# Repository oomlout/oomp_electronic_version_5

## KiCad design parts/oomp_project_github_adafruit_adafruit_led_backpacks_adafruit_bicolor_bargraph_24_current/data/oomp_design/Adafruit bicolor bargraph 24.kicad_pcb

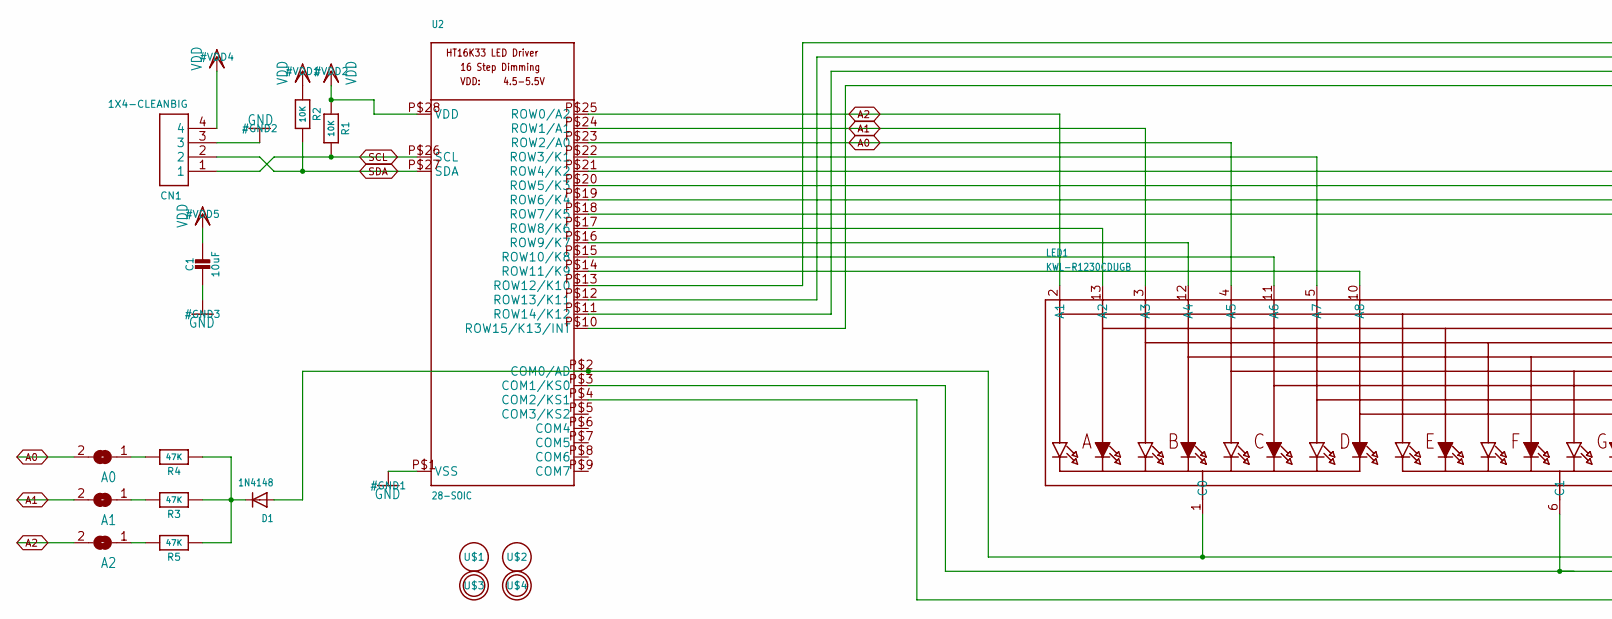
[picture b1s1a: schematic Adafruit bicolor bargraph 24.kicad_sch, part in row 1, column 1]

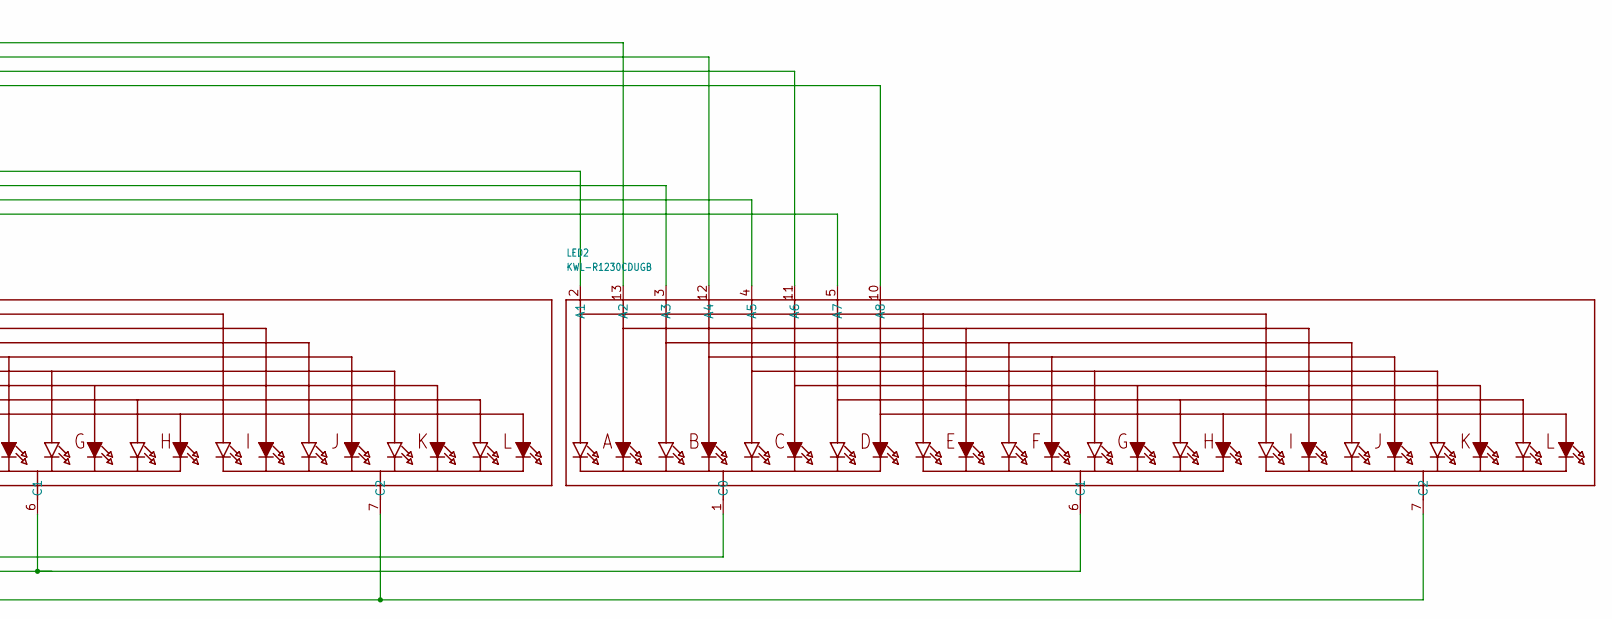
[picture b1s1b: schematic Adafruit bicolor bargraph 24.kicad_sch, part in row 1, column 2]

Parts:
A0, A1, A2: SOLDERJUMPERREFLOW_NOPASTE; SOLDERJUMPER_REFLOW_NOPASTE
C1: 10uF; 0805-NO
CN1: 1X4-CLEANBIG; 1X04-CLEANBIG
D1: 1N4148; SOD-323F
LED1, LED2: KWL-R1230CDUGB; SEGMENT_BICOL_BL-AR12Z3010
R1, R2: 10K; 0805-NO
R3, R4, R5: 47K; 0805-NO
U2: 28-SOIC; SOP28_300MIL
U$1, U$2: FIDUCIAL; FIDUCIAL_1MM
U$3, U$4: MOUNTINGHOLE2.5; MOUNTINGHOLE_2.5_PLATED

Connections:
A0: A0.2, LED1.4 (A5), U2.P$23 (ROW2/A0)
A1: A1.2, LED1.3 (A3), U2.P$24 (ROW1/A1)
A2: A2.2, LED1.2 (A1), U2.P$25 (ROW0/A2)
C0: D1.A, LED1.1 (C0), LED2.1 (C0), U2.P$2 (COM0/AD)
C1: LED1.6 (C1), LED2.6 (C1), U2.P$3 (COM1/KS0)
C2: LED1.7 (C2), LED2.7 (C2), U2.P$4 (COM2/KS1)
GND: C1.2, CN1.3, U2.P$1 (VSS)
unnamed: LED2.5 (A7), U2.P$18 (ROW7/K5)
unnamed: LED1.13 (A2), U2.P$17 (ROW8/K6)
unnamed: LED2.4 (A5), U2.P$19 (ROW6/K4)
unnamed: A2.1, R5.2
unnamed: D1.C, R3.1, R4.1, R5.1
unnamed: A1.1, R3.2
unnamed: A0.1, R4.2
unnamed: LED2.2 (A1), U2.P$21 (ROW4/K2)
unnamed: LED1.5 (A7), U2.P$22 (ROW3/K1)
unnamed: LED2.3 (A3), U2.P$20 (ROW5/K3)
unnamed: LED1.12 (A4), U2.P$16 (ROW9/K7)
R10: LED1.11 (A6), U2.P$15 (ROW10/K8)
R11: LED1.10 (A8), U2.P$14 (ROW11/K9)
R12: LED2.13 (A2), U2.P$13 (ROW12/K10)
R13: LED2.12 (A4), U2.P$12 (ROW13/K11)
R14: LED2.11 (A6), U2.P$11 (ROW14/K12)
R15: LED2.10 (A8), U2.P$10 (ROW15/K13/INT)
SCL: CN1.1, R1.2, U2.P$26 (SCL)
SDA: CN1.2, R2.2, U2.P$27 (SDA)
VDD: C1.1, CN1.4, R1.1, R2.1, U2.P$28 (VDD)

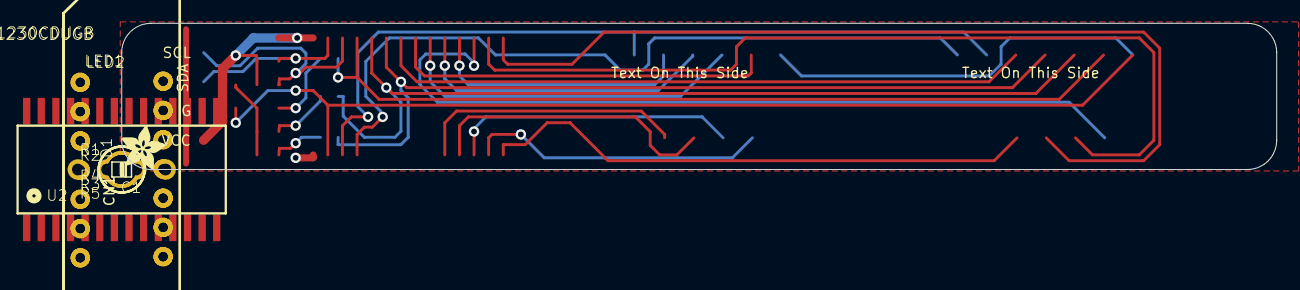
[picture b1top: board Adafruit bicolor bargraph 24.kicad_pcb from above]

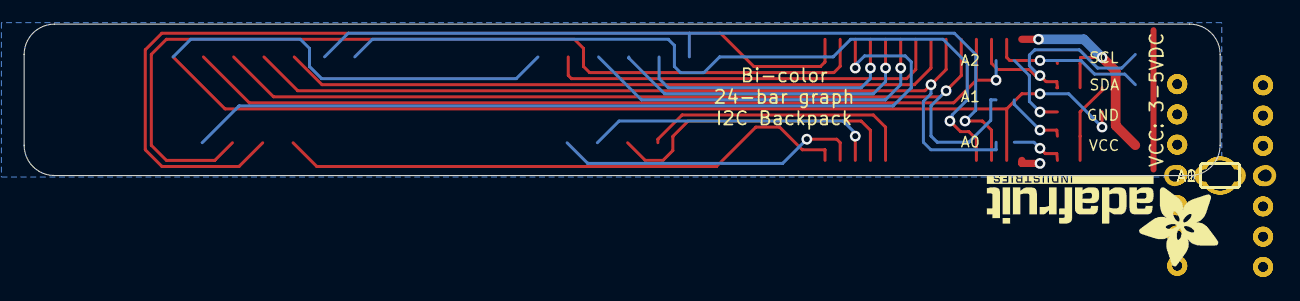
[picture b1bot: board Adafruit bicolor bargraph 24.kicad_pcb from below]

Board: 2 copper layers, 100.3 x 12.7 mm, 20 parts (4 on the bottom side), 27 nets.

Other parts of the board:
U$5: ADAFRUIT_TEXT_20MM
U$6: ADAFRUIT_3.5MM

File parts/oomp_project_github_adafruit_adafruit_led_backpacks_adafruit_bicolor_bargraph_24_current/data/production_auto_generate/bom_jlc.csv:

Comment,Designator,Footprint,LCSC Part #
,U$6,Adafruit bicolor bargraph 24-import-fps:ADAFRUIT_3.5MM,
,U$5,Adafruit bicolor bargraph 24-import-fps:ADAFRUIT_TEXT_20MM,
,"A0,A1,A2",Adafruit bicolor bargraph 24-import-fps:SOLDERJUMPER_REFLOW_NOPASTE,
10K,"R1,R2",Adafruit bicolor bargraph 24-import-fps:0805-NO,C17414
10uF,C1,Adafruit bicolor bargraph 24-import-fps:0805-NO,
1N4148,D1,Adafruit bicolor bargraph 24-import-fps:SOD-323F,
1X4-CLEANBIG,CN1,Adafruit bicolor bargraph 24-import-fps:1X04-CLEANBIG,
28-SOIC,U2,Adafruit bicolor bargraph 24-import-fps:SOP28_300MIL,
47K,"R3,R4,R5",Adafruit bicolor bargraph 24-import-fps:0805-NO,C17713
FIDUCIAL,"U$1,U$2",Adafruit bicolor bargraph 24-import-fps:FIDUCIAL_1MM,
KWL-R1230CDUGB,"LED1,LED2",Adafruit bicolor bargraph 24-import-fps:SEGMENT_BICOL_BL-AR12Z3010,

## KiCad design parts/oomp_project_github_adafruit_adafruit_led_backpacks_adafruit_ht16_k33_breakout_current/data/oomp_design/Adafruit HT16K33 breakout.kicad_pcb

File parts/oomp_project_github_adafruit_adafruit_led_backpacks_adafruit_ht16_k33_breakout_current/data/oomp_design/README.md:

# OOMP KiCad design copy

Open `Adafruit HT16K33 breakout.kicad_pro` (or the `.kicad_pcb` / `.kicad_sch`) in KiCad. Local OOMP libraries are under `libraries/`. Original inputs are preserved in [../original/](../original/).

Only verified unchanged installed KiCad defaults were renamed. Modified, custom, unmatched and unavailable items remain unchanged. Soldering variants are never swapped during conversion. Existing pad coordinates, nets and UUIDs are preserved.

See [conversion_report.yaml](conversion_report.yaml) for every conversion and skip. Copy this directory before editing; regeneration refuses to overwrite edited design files.

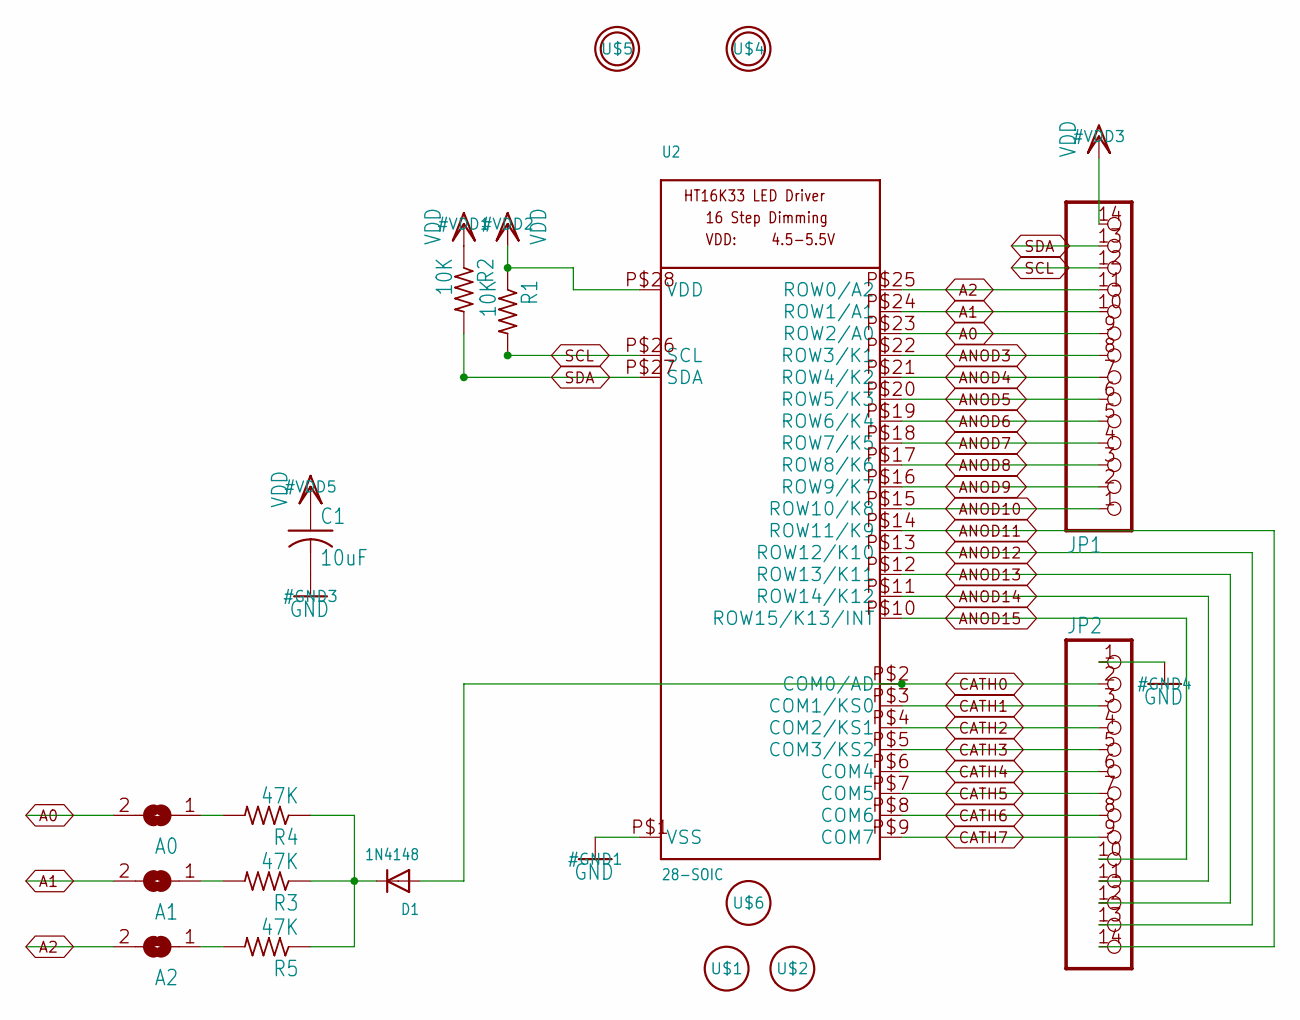
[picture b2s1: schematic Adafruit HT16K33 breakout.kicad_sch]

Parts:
A0, A1, A2: SOLDERJUMPERREFLOW_NOPASTE; SOLDERJUMPER_REFLOW_NOPASTE
C1: 10uF; C0805
D1: 1N4148; SOD-323F
JP1, JP2: PINHD-1X14-CB; 1X14-CB
R1, R2: 10K; R0805
R3, R4, R5: 47K; R0805
U2: 28-SOIC; SOP28_300MIL
U$1, U$2, U$6: FIDUCIAL; FIDUCIAL_1MM
U$4, U$5: MOUNTINGHOLE2.5; MOUNTINGHOLE_2.5_PLATED

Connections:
A0: A0.2, JP1.9, U2.P$23 (ROW2/A0)
A1: A1.2, JP1.10, U2.P$24 (ROW1/A1)
A2: A2.2, JP1.11, U2.P$25 (ROW0/A2)
ANOD3: JP1.8, U2.P$22 (ROW3/K1)
ANOD4: JP1.7, U2.P$21 (ROW4/K2)
ANOD5: JP1.6, U2.P$20 (ROW5/K3)
ANOD6: JP1.5, U2.P$19 (ROW6/K4)
ANOD7: JP1.4, U2.P$18 (ROW7/K5)
ANOD8: JP1.3, U2.P$17 (ROW8/K6)
ANOD9: JP1.2, U2.P$16 (ROW9/K7)
ANOD10: JP1.1, U2.P$15 (ROW10/K8)
ANOD11: JP2.14, U2.P$14 (ROW11/K9)
ANOD12: JP2.13, U2.P$13 (ROW12/K10)
ANOD13: JP2.12, U2.P$12 (ROW13/K11)
ANOD14: JP2.11, U2.P$11 (ROW14/K12)
ANOD15: JP2.10, U2.P$10 (ROW15/K13/INT)
CATH0: D1.A, JP2.2, U2.P$2 (COM0/AD)
CATH1: JP2.3, U2.P$3 (COM1/KS0)
CATH2: JP2.4, U2.P$4 (COM2/KS1)
CATH3: JP2.5, U2.P$5 (COM3/KS2)
CATH4: JP2.6, U2.P$6 (COM4)
CATH5: JP2.7, U2.P$7 (COM5)
CATH6: JP2.8, U2.P$8 (COM6)
CATH7: JP2.9, U2.P$9 (COM7)
GND: C1.2, JP2.1, U2.P$1 (VSS)
unnamed: A2.1, R5.2
unnamed: D1.C, R3.1, R4.1, R5.1
unnamed: A1.1, R3.2
unnamed: A0.1, R4.2
SCL: JP1.12, R1.2, U2.P$26 (SCL)
SDA: JP1.13, R2.2, U2.P$27 (SDA)
VDD: C1.1, JP1.14, R1.1, R2.1, U2.P$28 (VDD)

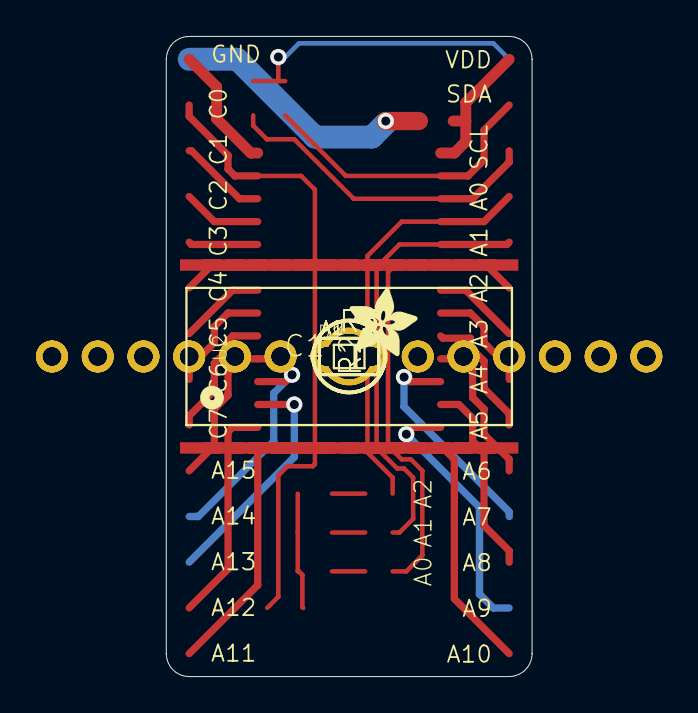
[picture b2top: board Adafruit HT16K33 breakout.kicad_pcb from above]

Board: 16 copper layers, 20.3 x 35.6 mm, 20 parts (1 on the bottom side), 32 nets.

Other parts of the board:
U$3: ADAFRUIT_3.5MM
U$7: ADAFRUIT_5MM

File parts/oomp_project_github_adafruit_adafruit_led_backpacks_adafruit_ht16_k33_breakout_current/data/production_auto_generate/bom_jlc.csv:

Comment,Designator,Footprint,LCSC Part #
,"JP1,JP2",Adafruit HT16K33 breakout-import-fps:1X14-CB,C2905490
,U$3,Adafruit HT16K33 breakout-import-fps:ADAFRUIT_3.5MM,
,U$7,Adafruit HT16K33 breakout-import-fps:ADAFRUIT_5MM,
,"A0,A1,A2",Adafruit HT16K33 breakout-import-fps:SOLDERJUMPER_REFLOW_NOPASTE,
10K,"R1,R2",Adafruit HT16K33 breakout-import-fps:R0805,C17414
10uF,C1,Adafruit HT16K33 breakout-import-fps:C0805,
1N4148,D1,Adafruit HT16K33 breakout-import-fps:SOD-323F,
28-SOIC,U2,Adafruit HT16K33 breakout-import-fps:SOP28_300MIL,
47K,"R3,R4,R5",Adafruit HT16K33 breakout-import-fps:R0805,C17713
FIDUCIAL,"U$1,U$2,U$6",Adafruit HT16K33 breakout-import-fps:FIDUCIAL_1MM,

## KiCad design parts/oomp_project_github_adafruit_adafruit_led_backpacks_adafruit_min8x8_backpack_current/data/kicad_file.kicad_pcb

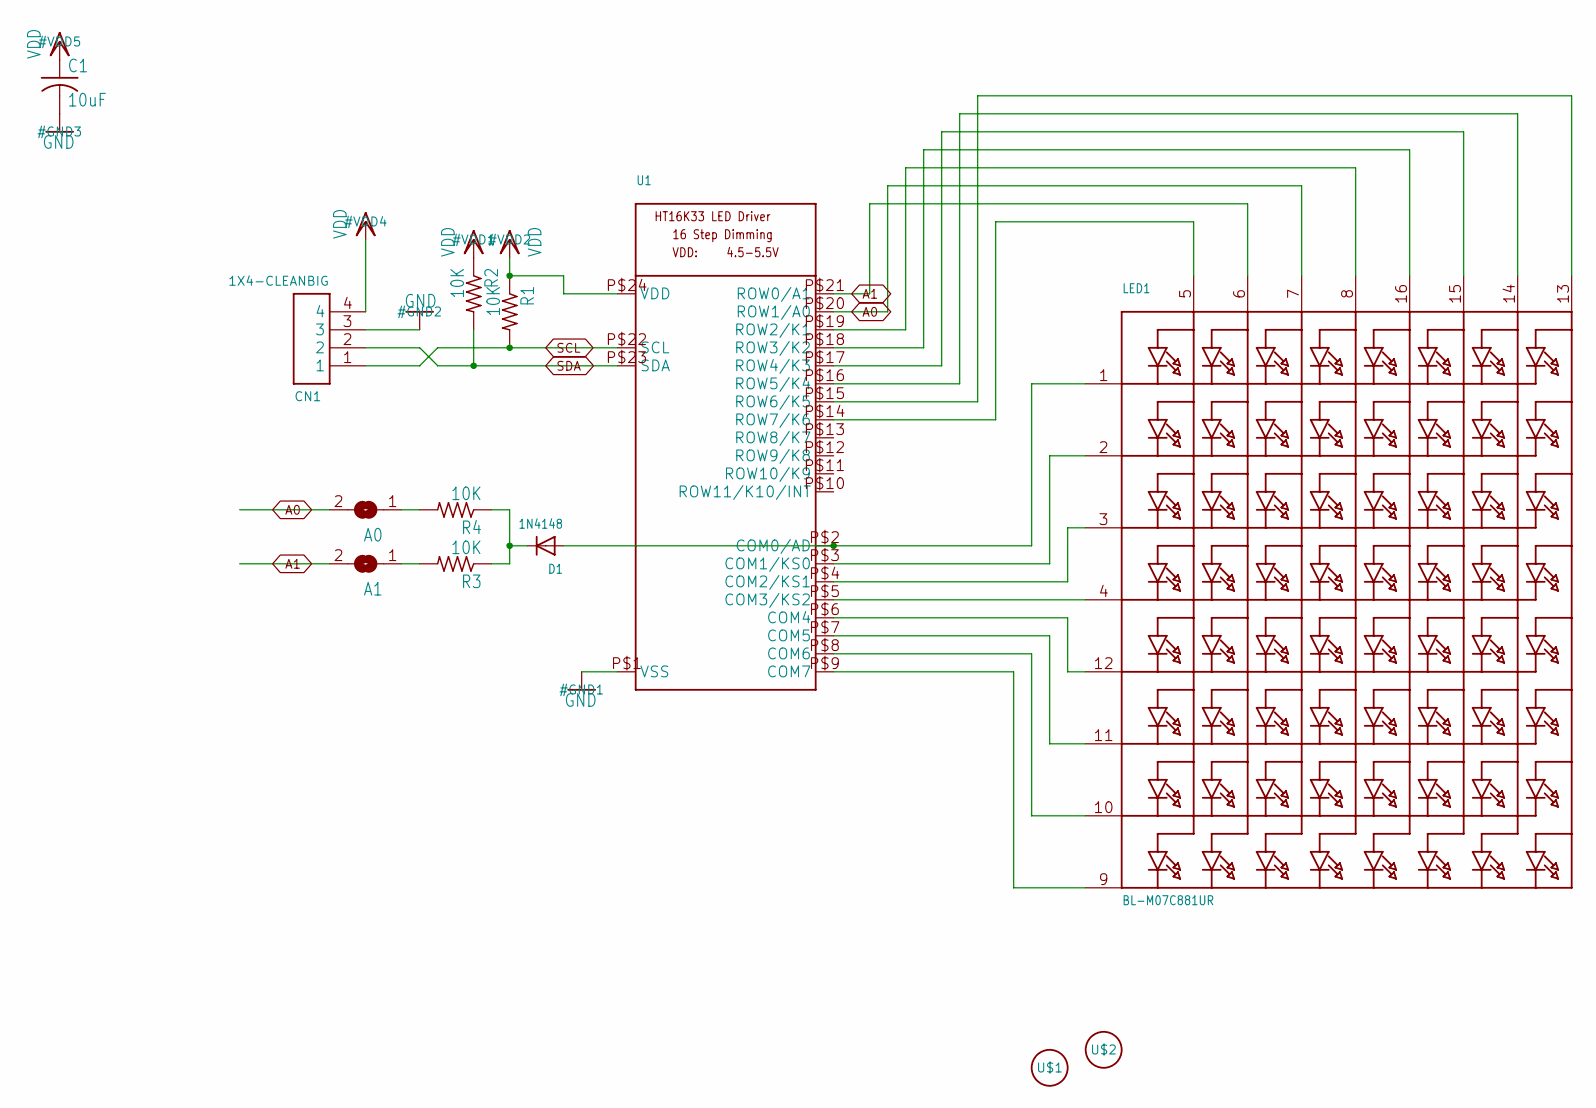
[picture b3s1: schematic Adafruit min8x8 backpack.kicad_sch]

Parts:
A0, A1: SOLDERJUMPERREFLOW_NOPASTE; SOLDERJUMPER_REFLOW_NOPASTE
C1: 10uF; C0805
CN1: 1X4-CLEANBIG; 1X04-CLEANBIG
D1: 1N4148; SOD-323F
LED1: BL-M07C881UR; SEGMENT_BL-M07C881UR
R1, R2, R3, R4: 10K; R0805
U1: HT16K33_SOP24; SOP24_300MIL
U$1, U$2: FIDUCIAL; FIDUCIAL_1MM

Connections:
A0: A0.2, LED1.7 (A3), U1.P$20 (ROW1/A0)
A1: A1.2, LED1.6 (A2), U1.P$21 (ROW0/A1)
GND: C1.2, CN1.3, U1.P$1 (VSS)
unnamed: LED1.9 (K8), U1.P$9 (COM7)
unnamed: LED1.10 (K7), U1.P$8 (COM6)
unnamed: LED1.11 (K6), U1.P$7 (COM5)
unnamed: LED1.12 (K5), U1.P$6 (COM4)
unnamed: LED1.4 (K4), U1.P$5 (COM3/KS2)
unnamed: LED1.3 (K3), U1.P$4 (COM2/KS1)
unnamed: LED1.2 (K2), U1.P$3 (COM1/KS0)
unnamed: D1.A, LED1.1 (K1), U1.P$2 (COM0/AD)
unnamed: LED1.8 (A4), U1.P$19 (ROW2/K1)
unnamed: LED1.16 (A5), U1.P$18 (ROW3/K2)
unnamed: LED1.15 (A6), U1.P$17 (ROW4/K3)
unnamed: D1.C, R3.1, R4.1
unnamed: LED1.5 (A1), U1.P$14 (ROW7/K6)
unnamed: A1.1, R3.2
unnamed: A0.1, R4.2
SCL: CN1.1, R1.2, U1.P$22 (SCL)
SDA: CN1.2, R2.2, U1.P$23 (SDA)
SEG_F: LED1.14 (A7), U1.P$16 (ROW5/K4)
SEG_G: LED1.13 (A8), U1.P$15 (ROW6/K5)
VDD: C1.1, CN1.4, R1.1, R2.1, U1.P$24 (VDD)

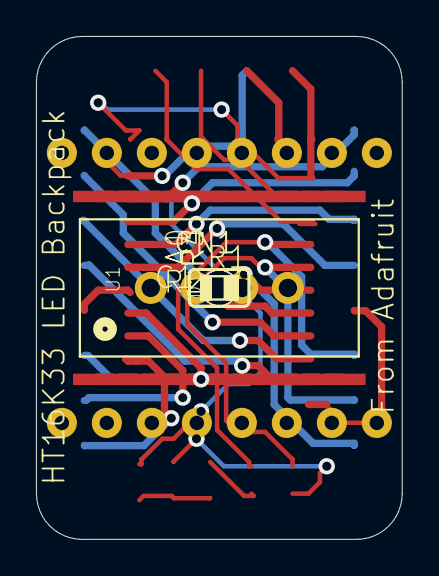
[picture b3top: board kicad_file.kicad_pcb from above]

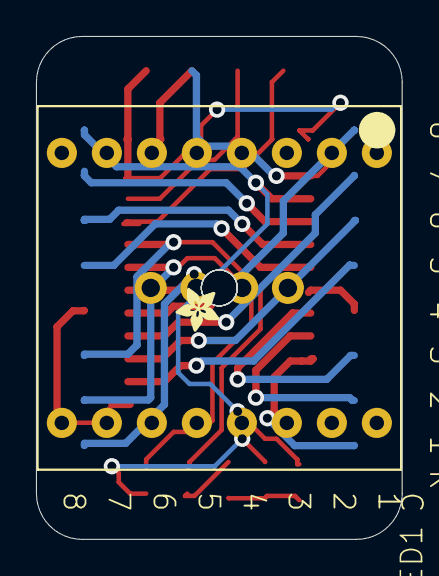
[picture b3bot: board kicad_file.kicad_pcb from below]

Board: 16 copper layers, 20.3 x 27.9 mm, 18 parts (2 on the bottom side), 23 nets.

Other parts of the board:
U$4: ADAFRUIT_2.5MM
UNK_HOLE_0: dummyfp0
UNK_HOLE_1: dummyfp1
UNK_HOLE_2: dummyfp2
UNK_HOLE_3: dummyfp3

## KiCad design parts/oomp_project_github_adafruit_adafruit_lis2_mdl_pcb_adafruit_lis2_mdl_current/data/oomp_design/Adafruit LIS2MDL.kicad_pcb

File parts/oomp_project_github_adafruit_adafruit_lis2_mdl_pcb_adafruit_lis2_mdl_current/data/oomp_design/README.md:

# OOMP KiCad design copy

Open `Adafruit LIS2MDL.kicad_pro` (or the `.kicad_pcb` / `.kicad_sch`) in KiCad. Local OOMP libraries are under `libraries/`. Original inputs are preserved in [../original/](../original/).

Only verified unchanged installed KiCad defaults were renamed. Modified, custom, unmatched and unavailable items remain unchanged. Soldering variants are never swapped during conversion. Existing pad coordinates, nets and UUIDs are preserved.

See [conversion_report.yaml](conversion_report.yaml) for every conversion and skip. Copy this directory before editing; regeneration refuses to overwrite edited design files.

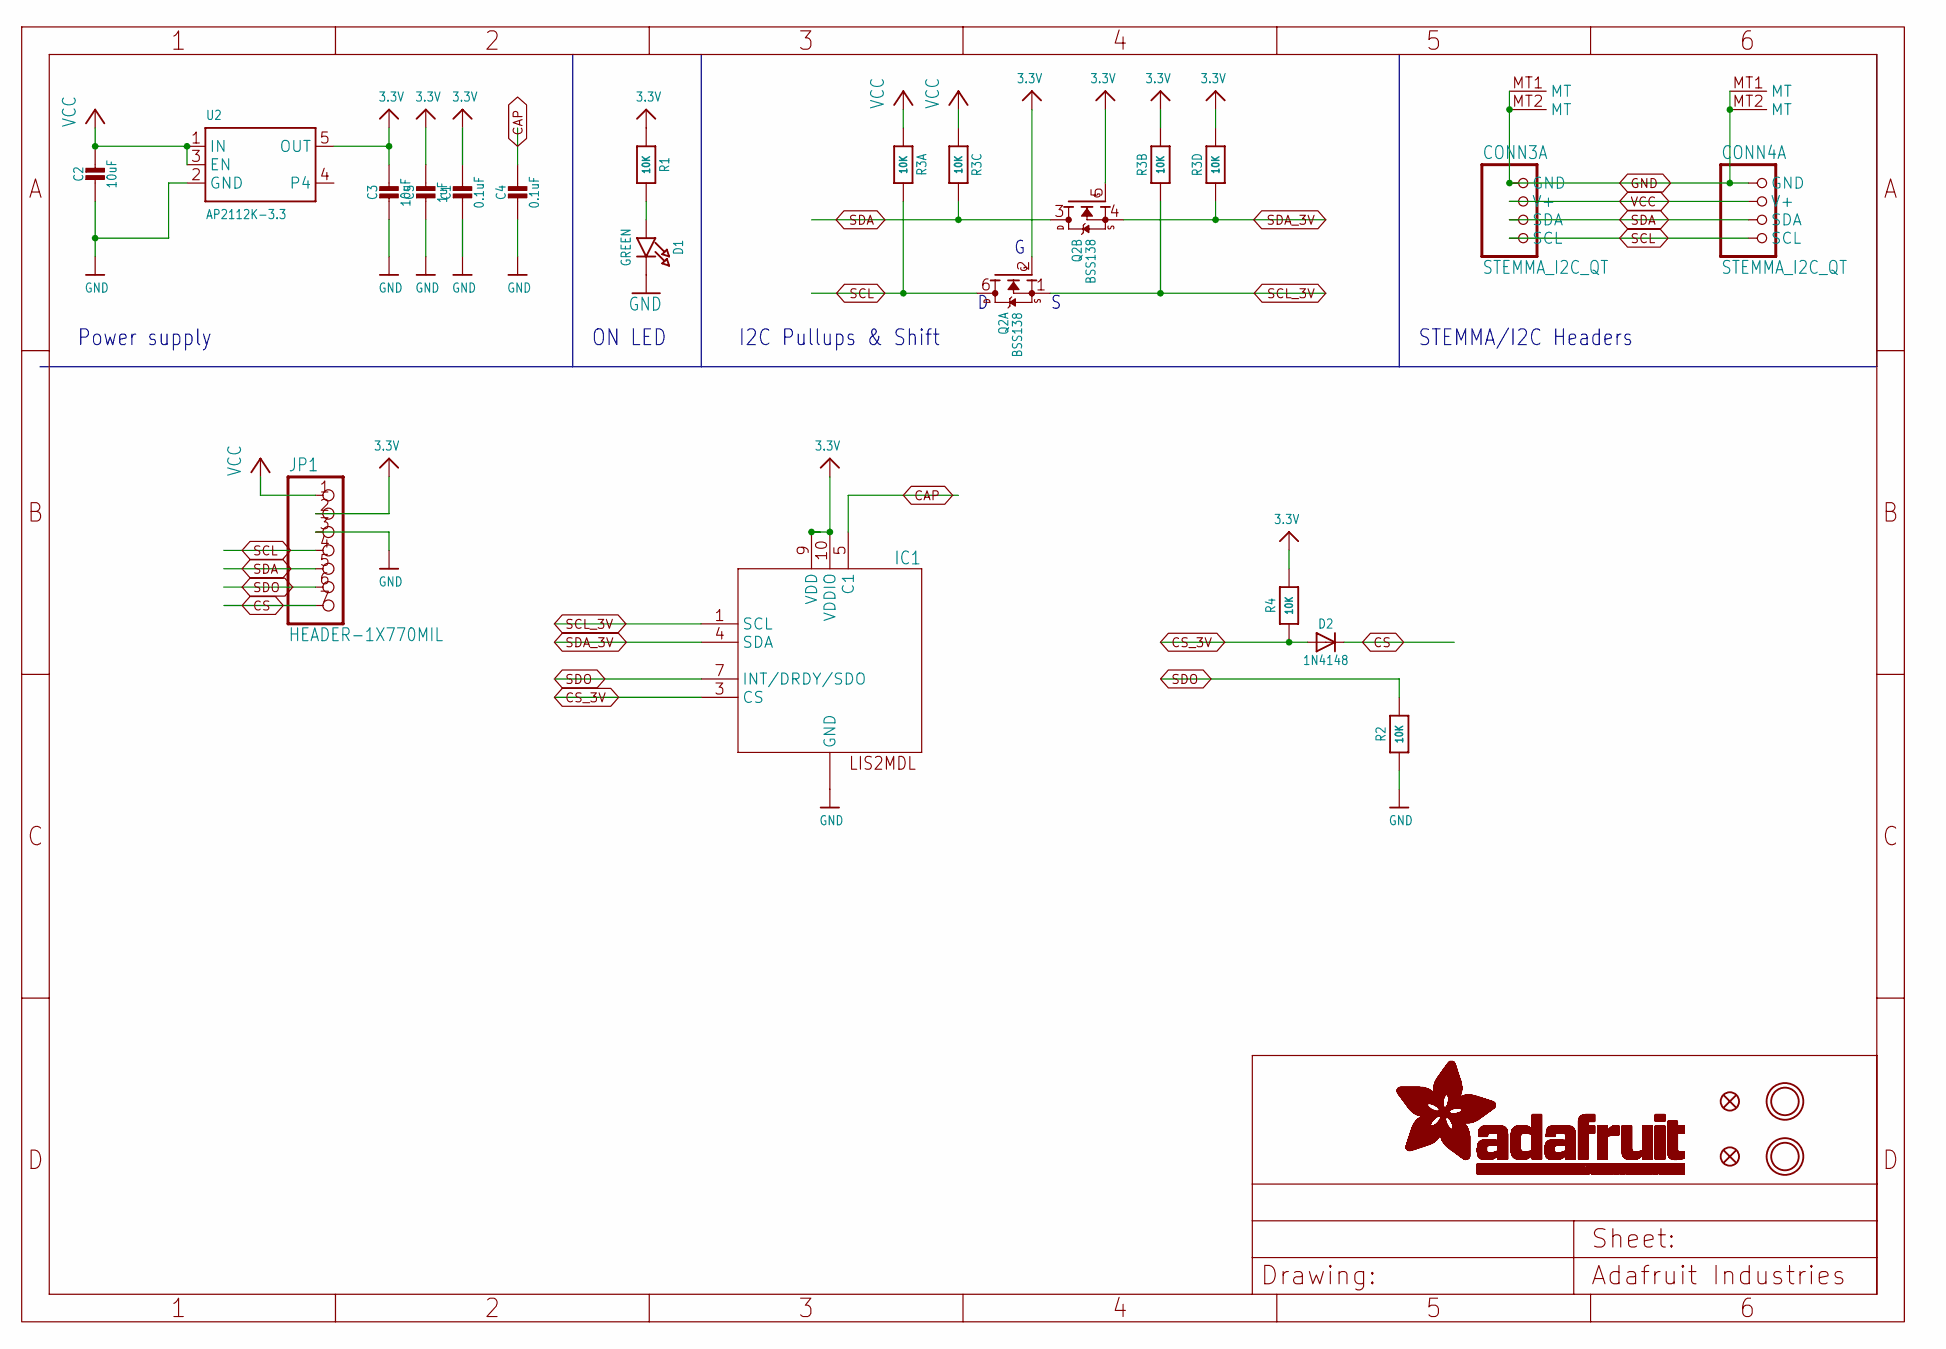
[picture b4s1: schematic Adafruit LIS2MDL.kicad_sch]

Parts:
C1, C4: 0.1uF; 0603-NO
C2, C3: 10uF; 0805-NO
C5: 1uF; 0603-NO
CONN3, CONN4: STEMMA_I2C_QT; JST_SH4
D1: GREEN; CHIPLED_0603_NOOUTLINE
D2: 1N4148; SOD-323
FID3, FID4: FIDUCIAL_1MM
IC1: LIS2MDL; LGA12_2X2MM
JP1: HEADER-1X770MIL; 1X07_ROUND_70
Q2: BSS138; SOT363
R1, R2, R4: 10K; 0603-NO
R3: 10K; RESPACK_4X0603
U2: AP2112K-3.3; SOT23-5
U$1, U$17: MOUNTINGHOLE2.5; MOUNTINGHOLE_2.5_PLATED

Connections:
3.3V: C1.1, C3.1, C5.1, IC1.9 (VDD), IC1.10 (VDDIO), JP1.2, Q2.2 (G), Q2.5 (G), R1.1, R3.2 (1), R3.4 (1), R4.2, U2.5 (OUT)
CAP: C4.1, IC1.5 (C1)
CS: D2.C, JP1.7
CS_3V: D2.A, IC1.3 (CS), R4.1
GND: C1.2, C2.2, C3.2, C4.2, C5.2, CONN3.1 (GND), CONN3.MT1 (MT), CONN3.MT2 (MT), CONN4.1 (GND), CONN4.MT1 (MT), CONN4.MT2 (MT), D1.C, IC1.2 (GND), IC1.6 (GND), IC1.8 (GND), IC1.11 (GND), IC1.12 (GND), JP1.3, R2.1, U2.2 (GND)
unnamed: D1.A, R1.2
SCL: CONN3.4 (SCL), CONN4.4 (SCL), JP1.4, Q2.6 (D), R3.8 (2)
SCL_3V: IC1.1 (SCL), Q2.1 (S), R3.7 (2)
SDA: CONN3.3 (SDA), CONN4.3 (SDA), JP1.5, Q2.3 (D), R3.6 (2)
SDA_3V: IC1.4 (SDA), Q2.4 (S), R3.5 (2)
SDO: IC1.7 (INT/DRDY/SDO), JP1.6, R2.2
VCC: C2.1, CONN3.2 (V+), CONN4.2 (V+), JP1.1, R3.1, R3.3 (1), U2.1 (IN), U2.3 (EN)

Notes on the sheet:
Power supply
STEMMA/I2C Headers
I2C Pullups & Shift
ON LED

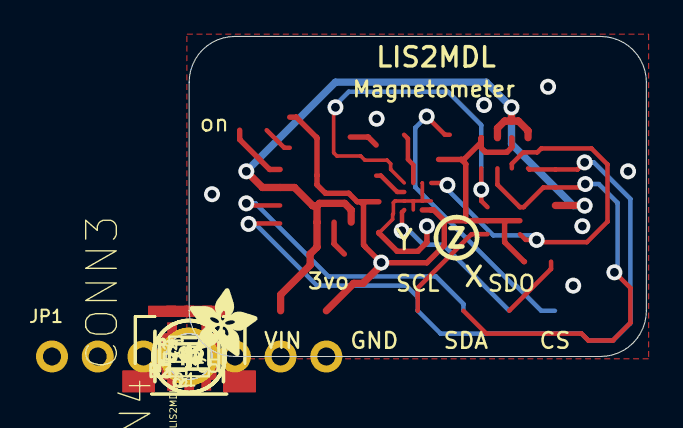
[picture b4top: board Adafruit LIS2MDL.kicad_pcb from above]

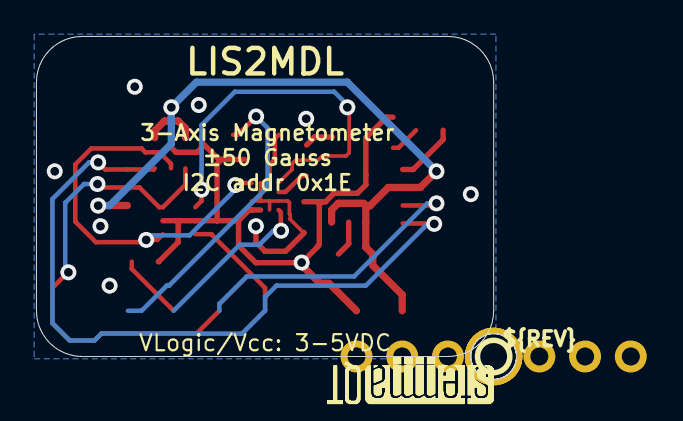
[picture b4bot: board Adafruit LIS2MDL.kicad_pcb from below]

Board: 2 copper layers, 25.4 x 17.8 mm, 27 parts (3 on the bottom side), 12 nets.

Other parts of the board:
U$11: ADAFRUIT_3.5MM
U$25: PCBFEAT-REV-040
U$30, U$31: STEMMAQT
UNK_HOLE_0: dummyfp0
UNK_HOLE_1: dummyfp1

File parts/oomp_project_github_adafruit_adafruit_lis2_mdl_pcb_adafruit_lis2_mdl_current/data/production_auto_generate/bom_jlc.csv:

Comment,Designator,Footprint,LCSC Part #
,JP1,Adafruit LIS2MDL-import-fps:1X07_ROUND_70,C7501585
,U$11,Adafruit LIS2MDL-import-fps:ADAFRUIT_3.5MM,
,U$25,Adafruit LIS2MDL-import-fps:PCBFEAT-REV-040,
,"U$30,U$31",Adafruit LIS2MDL-import-fps:STEMMAQT,
0.1uF,"C1,C4",Adafruit LIS2MDL-import-fps:0603-NO,C14663
10K,"R1,R2,R4",Adafruit LIS2MDL-import-fps:0603-NO,C98220
10K,R3,Adafruit LIS2MDL-import-fps:RESPACK_4X0603,C98220
10uF,"C2,C3",Adafruit LIS2MDL-import-fps:0805-NO,
1N4148,D2,Adafruit LIS2MDL-import-fps:SOD-323,
1uF,C5,Adafruit LIS2MDL-import-fps:0603-NO,C5673
AP2112K-3.3,U2,Adafruit LIS2MDL-import-fps:SOT23-5,
BSS138,Q2,Adafruit LIS2MDL-import-fps:SOT363,
GREEN,D1,Adafruit LIS2MDL-import-fps:CHIPLED_0603_NOOUTLINE,
LIS2MDL,IC1,Adafruit LIS2MDL-import-fps:LGA12_2X2MM,
STEMMA_I2C_QT,"CONN3,CONN4",Adafruit LIS2MDL-import-fps:JST_SH4,C160404
